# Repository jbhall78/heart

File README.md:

Heart
Heart Shaped LED Circuit
<hr>

<hr>

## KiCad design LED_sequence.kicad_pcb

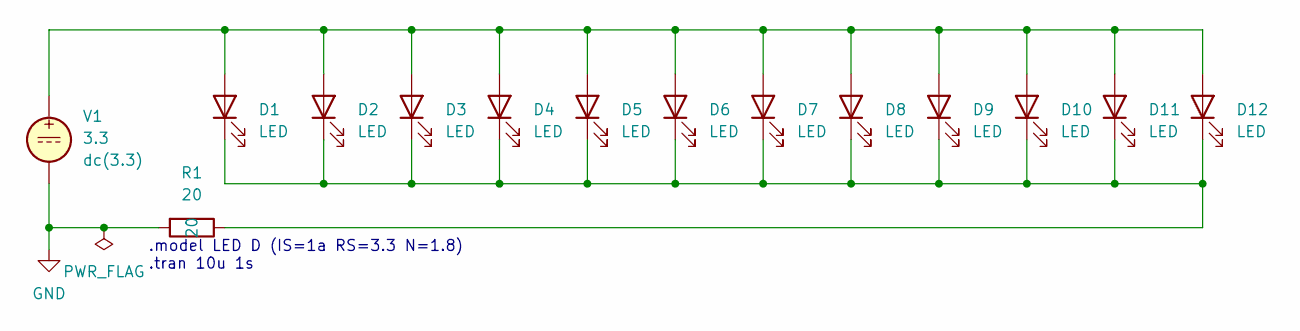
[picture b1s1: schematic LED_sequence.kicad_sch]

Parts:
D1, D2, D3, D4, D5, D6, D7, D8, D9, D10, D11, D12: LED; LED_D5.0mm
R1: 20; R_Axial_DIN0207_L6.3mm_D2.5mm_P10.16mm_Horizontal
V1: 3.3; TerminalBlock_bornier-2_P5.08mm

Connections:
GND: R1.2, V1.2
unnamed: D1.1 (K), D2.1 (K), D3.1 (K), D4.1 (K), D5.1 (K), D6.1 (K), D7.1 (K), D8.1 (K), D9.1 (K), D10.1 (K), D11.1 (K), D12.1 (K), R1.1
unnamed: D1.2 (A), D2.2 (A), D3.2 (A), D4.2 (A), D5.2 (A), D6.2 (A), D7.2 (A), D8.2 (A), D9.2 (A), D10.2 (A), D11.2 (A), D12.2 (A), V1.1

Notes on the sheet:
.model LED D (IS=1a RS=3.3 N=1.8) .tran 10u 1s

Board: 2 copper layers, 14 parts (0 on the bottom side), 3 nets, no tracks yet.

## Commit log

2023-03-10 Added Photos and README
2023-03-10 Initial commit of LTSpice and KiKad schematics
